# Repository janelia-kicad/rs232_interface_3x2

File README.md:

# rs232_interface_3x2

Authors:

    Peter Polidoro <polidorop@janelia.hhmi.org>

License:

    BSD

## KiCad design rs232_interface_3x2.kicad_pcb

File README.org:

#+TITLE: rs232_interface_3x2
#+AUTHOR: Peter Polidoro
#+EMAIL: peter@polidoro.io

* Repository Information
  - Author :: Peter Polidoro
  - License :: Open-Source Hardware

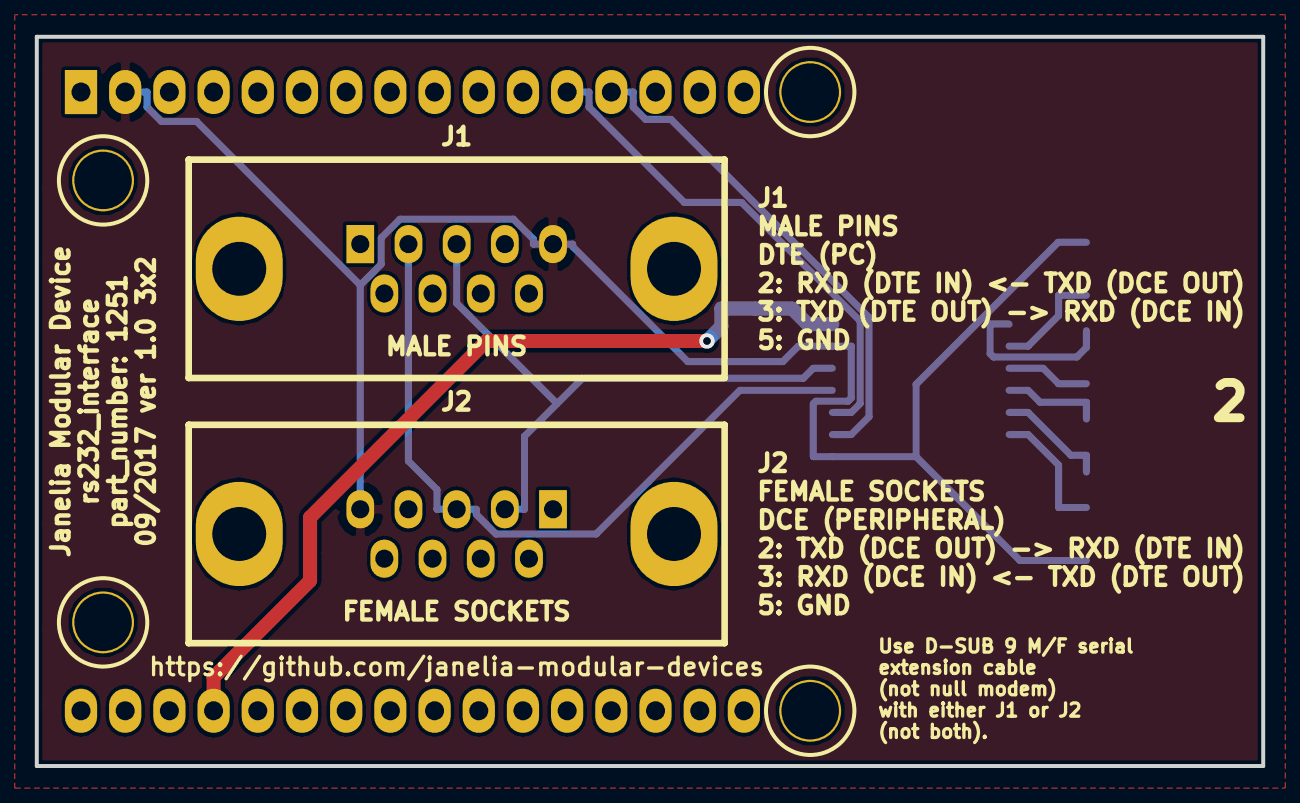
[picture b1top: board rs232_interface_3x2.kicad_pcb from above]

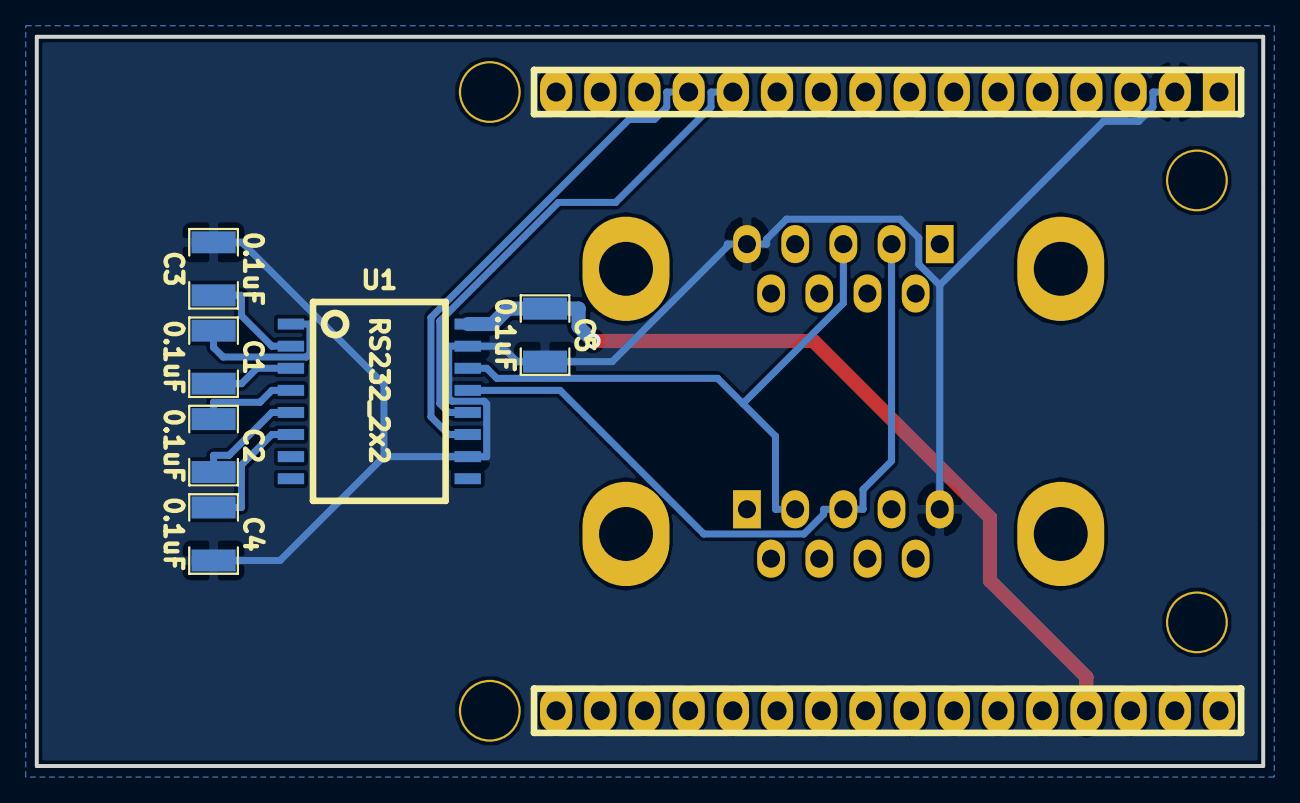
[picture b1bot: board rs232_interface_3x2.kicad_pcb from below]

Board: 2 copper layers, 70.5 x 41.9 mm, 9 parts (6 on the bottom side), 12 nets.

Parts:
C1, C2, C3, C4, C5: 0.1uF; SM1210
J1: DB9M
J2: DB9F
MDB1: MODULAR_DEVICE_BASE_3X2_MALE
U1: RS232_2x2; SOIC_16

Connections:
+3V3: C5.1, MDB1.3V3, U1.16
/RX2: MDB1.9, U1.12
/RXD: J1.2, J2.3, U1.13
/TX2: MDB1.10, U1.11
/TXD: J1.3, J2.2, U1.14
GND: C3.2, C4.2, C5.2, J1.5, J2.5, MDB1.GND, U1.10, U1.15
unnamed: C1.1, U1.1
unnamed: C1.2, U1.3
unnamed: C2.1, U1.4
unnamed: C2.2, U1.5
unnamed: C3.1, U1.2
unnamed: C4.1, U1.6

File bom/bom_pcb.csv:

Item,Reference(s),Value,Quantity,Description,PartNumber,Vendor
1,C1 C2 C3 C4 C5,0.1uF,5,CAP CER 0.1UF 50V 10% X7R 1210,399-13229-1-ND,digikey
2,J1,DB9M,1,CONN D-SUB PLUG 9POS VERT SOLDER,A126098-ND,digikey
3,J2,DB9F,1, CONN D-SUB RCPT 9POS VERT SOLDER,A115163-ND,digikey
4,MDB1,MODULAR_DEVICE_BASE_3X2_MALE,2,16 Position Header Through Hole Male Pins,S1011E-16-ND,digikey
5,U1,RS232_2x2,1,IC RS232 LINE DVR/RCVR 16-SOIC,296-33568-5-ND,digikey

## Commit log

2017-07-12 Initial commit.
2017-07-14 Updated edge positions.
2017-09-14 rs232 -> serial.
2017-09-15 Added RS232 components.
2017-09-15 Added 2 port RJ45.
2017-09-18 Added text to footprint.
2017-09-18 serial -> rs232.
2017-09-18 Progress towards v1.0.
2017-09-19 Finished v1.0.
2017-09-22 Removed extra libraries.
2018-01-08 Updated to v4.
2018-01-08 Updated gitignore.
2018-01-08 Removed *cache* and *rescue*.
2018-03-09 Update license from software to hardware.
2018-04-12 README.md -> README.org.
2018-04-19 Added .DS_Store to .gitignore.
2018-05-16 Added generate_kicad_documentation submodule.
2018-05-17 Updated submodules.
2018-08-12 Marked extra Teensy pins.
2018-08-12 Removed v4 files.
2018-08-24 Removed F.SilkS from pads.
2021-09-16 Update email address
2021-09-21 Remove ignored files
2022-02-22 Add guix files
2022-02-23 Add guix documentation
